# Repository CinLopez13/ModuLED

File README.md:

# ModuLED
Matriz led con doble función, Reloj Digital + Stacker Blocks

Es una Matriz de 18x7 que encontré en el LABI.

La idea es que tenga 2 funciones

Por un lado que sea un reloj digital para que quede en el LABI (a falta del reloj) 

Por otro lado quiero que tenga una función de "Game" para utilizar en los eventos del CDR (Como la feria del Libro o la Noche de los Museos). Este juego sería el stacker blocks

-> Dejo video de [Referencia](https://www.youtube.com/shorts/zlKPKK3Qink)

Para controlarlo decidí usar un modulo que controla matrices 8x8. Para cubrir todo el panel compré 3 modulos MAX7219 
Se va a programar con Arduino 

# Tareas 
- verificar que funcionan todos los Leds del panel 
- Soldar cables para conectar al modulo 
- Armar circuito con Arduino 
- Agregar mas Leds para hacer una matriz 24x7
- 

# Materiales
- Modulos MAX7219 x 3 
- Panel led del labi 
- Pines macho y hembra 
- Leds Rojo 3mm 
- Pistola de Silicona 

Objetivo: Una vez que funcione con Arduino la idea es programarlo con un ATMega del club (para esto hay que aprender a programar microcontroladores)

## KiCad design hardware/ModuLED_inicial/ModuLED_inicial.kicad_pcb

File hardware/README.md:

El modulo MAX7219 viene con un display 8x8 para usar. 
El objetivo es poder hacer esa matriz 8x8 (En realidad 8x7) pero con el panel que ya tenemos 

Se conectan al arduino VCC-GND-DIN-CS-CLK  Los pines donde esta DOUT son para conectar varios modulos 

Links de referencias para como utilizar el modulo MAX7219 

https://passionelectronique.fr/matrice-led-max7219-arduino/

https://www.pcbway.com/project/shareproject/LED_Dot_Matrix_MAX7219_1a67794a.html

https://www.14core.com/how-to-wire-8x8-matrix-led-with-max7219-on-arduino/

https://components101.com/displays/max7219-8x8-led-matrix-module

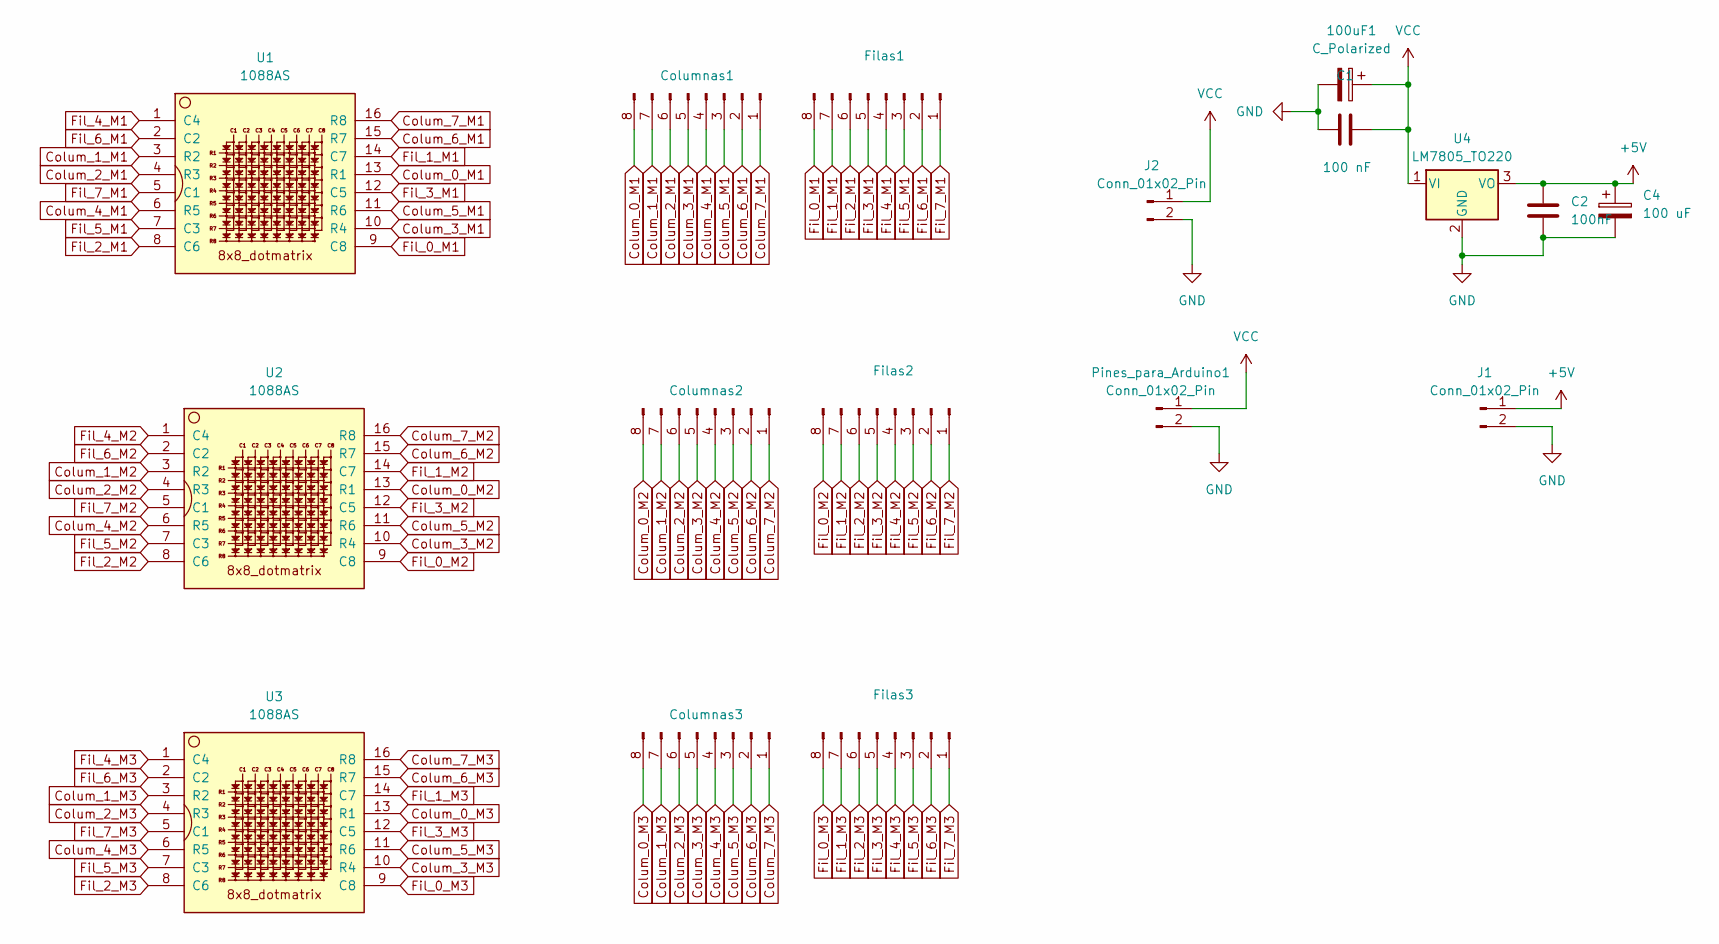
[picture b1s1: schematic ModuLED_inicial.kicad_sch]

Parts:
100uF1: C_Polarized; CP_Radial_D8.0mm_P2.50mm
C1: 100 nF; C_Disc_D3.4mm_W2.1mm_P2.50mm
C2: 100nF; C_Disc_D3.4mm_W2.1mm_P2.50mm
C4: 100 uF; CP_Radial_D8.0mm_P2.50mm
Columnas1, Columnas2, Columnas3: Conn_01x08_Pin; PinSocket_1x08_P2.54mm_Vertical
Filas1, Filas2, Filas3: Conn_01x08_Pin; PinSocket_1x08_P2.54mm_Vertical
J1: Conn_01x02_Pin; PinHeader_1x02_P2.54mm_Vertical
J2: Conn_01x02_Pin; Molex_KK-396_A-41791-0002_1x02_P3.96mm_Vertical
Pines_para_Arduino1: Conn_01x02_Pin; PinHeader_1x02_P2.54mm_Vertical
U1, U2, U3: 1088AS; LED_1088_Pin_Header
U4: LM7805_TO220; TO-220-3_Vertical

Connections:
+5V: C2.1, C4.1, J1.1, U4.3 (VO)
Colum_0_M1: Columnas1.8, U1.13 (R1)
Colum_0_M2: Columnas2.8, U2.13 (R1)
Colum_0_M3: Columnas3.8, U3.13 (R1)
Colum_1_M1: Columnas1.7, U1.3 (R2)
Colum_1_M2: Columnas2.7, U2.3 (R2)
Colum_1_M3: Columnas3.7, U3.3 (R2)
Colum_2_M1: Columnas1.6, U1.4 (R3)
Colum_2_M2: Columnas2.6, U2.4 (R3)
Colum_2_M3: Columnas3.6, U3.4 (R3)
Colum_3_M1: Columnas1.5, U1.10 (R4)
Colum_3_M2: Columnas2.5, U2.10 (R4)
Colum_3_M3: Columnas3.5, U3.10 (R4)
Colum_4_M1: Columnas1.4, U1.6 (R5)
Colum_4_M2: Columnas2.4, U2.6 (R5)
Colum_4_M3: Columnas3.4, U3.6 (R5)
Colum_5_M1: Columnas1.3, U1.11 (R6)
Colum_5_M2: Columnas2.3, U2.11 (R6)
Colum_5_M3: Columnas3.3, U3.11 (R6)
Colum_6_M1: Columnas1.2, U1.15 (R7)
Colum_6_M2: Columnas2.2, U2.15 (R7)
Colum_6_M3: Columnas3.2, U3.15 (R7)
Colum_7_M1: Columnas1.1, U1.16 (R8)
Colum_7_M2: Columnas2.1, U2.16 (R8)
Colum_7_M3: Columnas3.1, U3.16 (R8)
Fil_0_M1: Filas1.8, U1.9 (C8)
Fil_0_M2: Filas2.8, U2.9 (C8)
Fil_0_M3: Filas3.8, U3.9 (C8)
Fil_1_M1: Filas1.7, U1.14 (C7)
Fil_1_M2: Filas2.7, U2.14 (C7)
Fil_1_M3: Filas3.7, U3.14 (C7)
Fil_2_M1: Filas1.6, U1.8 (C6)
Fil_2_M2: Filas2.6, U2.8 (C6)
Fil_2_M3: Filas3.6, U3.8 (C6)
Fil_3_M1: Filas1.5, U1.12 (C5)
Fil_3_M2: Filas2.5, U2.12 (C5)
Fil_3_M3: Filas3.5, U3.12 (C5)
Fil_4_M1: Filas1.4, U1.1 (C4)
Fil_4_M2: Filas2.4, U2.1 (C4)
Fil_4_M3: Filas3.4, U3.1 (C4)
Fil_5_M1: Filas1.3, U1.7 (C3)
Fil_5_M2: Filas2.3, U2.7 (C3)
Fil_5_M3: Filas3.3, U3.7 (C3)
Fil_6_M1: Filas1.2, U1.2 (C2)
Fil_6_M2: Filas2.2, U2.2 (C2)
Fil_6_M3: Filas3.2, U3.2 (C2)
Fil_7_M1: Filas1.1, U1.5 (C1)
Fil_7_M2: Filas2.1, U2.5 (C1)
Fil_7_M3: Filas3.1, U3.5 (C1)
GND: 100uF1.2, C1.1, C2.2, C4.2, J1.2, J2.2, Pines_para_Arduino1.2, U4.2 (GND)
VCC: 100uF1.1, C1.2, J2.1, Pines_para_Arduino1.1, U4.1 (VI)

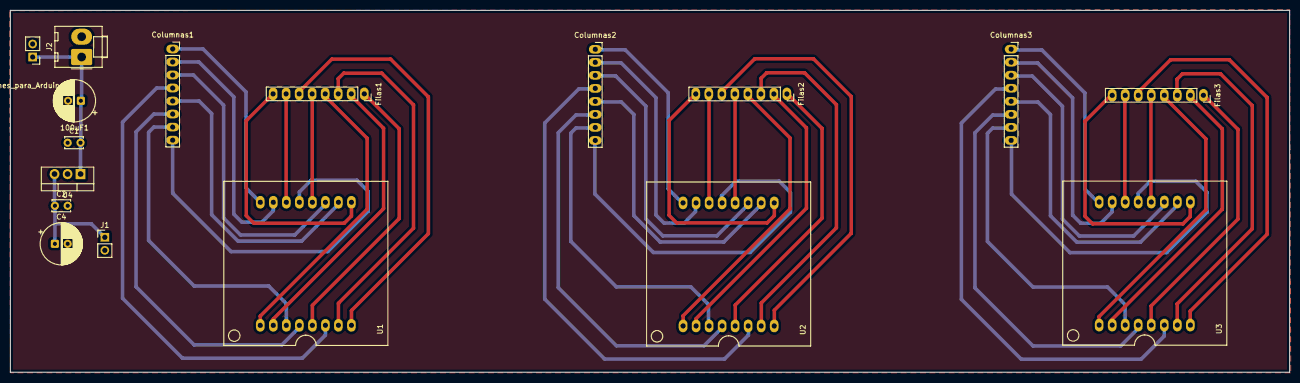
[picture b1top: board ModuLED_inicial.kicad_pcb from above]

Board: 2 copper layers, 249.5 x 70.6 mm, 17 parts (0 on the bottom side), 51 nets.

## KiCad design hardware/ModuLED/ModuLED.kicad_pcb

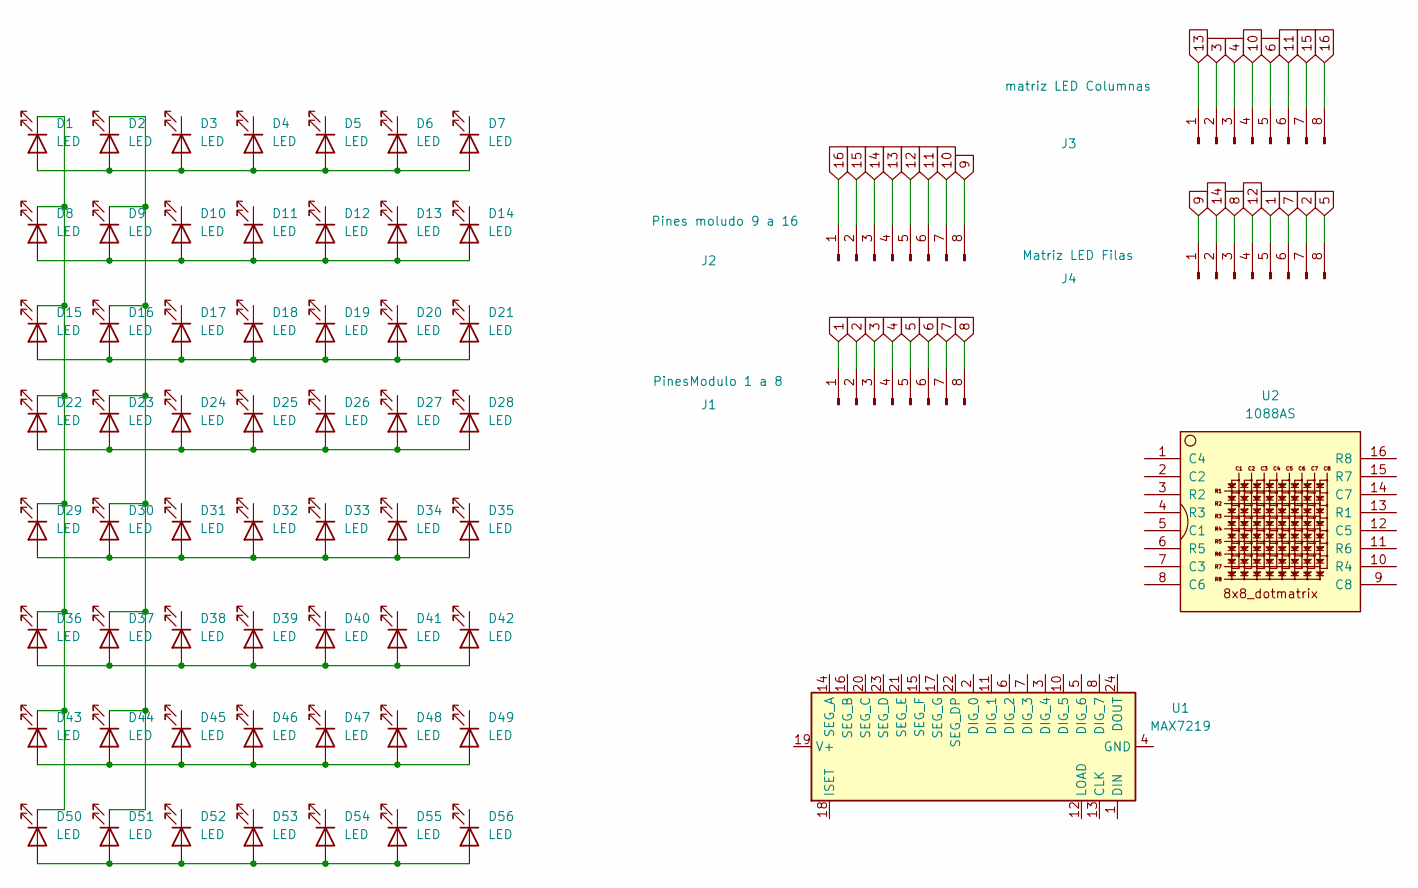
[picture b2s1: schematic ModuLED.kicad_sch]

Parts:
D1, D2, D3, D4, D5, D6, D7, D8, D9, D10, D11, D12, D13, D14, D15, D16, D17, D18, D19, D20, D21, D22, D23, D24, D25, D26, D27, D28, D29, D30, D31, D32, D33, D34, D35, D36, D37, D38, D39, D40, D41, D42, D43, D44, D45, D46, D47, D48, D49, D50, D51, D52, D53, D54, D55, D56: LED; LED_D3.0mm_Clear
J1: PinesModulo 1 a 8; Hirose_DF13-08P-1.25DSA_1x08_P1.25mm_Vertical
J2: Pines moludo 9 a 16; Hirose_DF13-08P-1.25DSA_1x08_P1.25mm_Vertical
J3: matriz LED Columnas; Hirose_DF13-08P-1.25DSA_1x08_P1.25mm_Vertical
J4: Matriz LED Filas; Hirose_DF13-08P-1.25DSA_1x08_P1.25mm_Vertical
U1: MAX7219; DIP-24_W7.62mm
U2: 1088AS; LED_1088_Pin_Header

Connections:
1: J1.1, J4.5
2: J1.2, J4.7
3: J1.3, J3.2
4: J1.4, J3.3
5: J1.5, J4.8
6: J1.6, J3.5
7: J1.7, J4.6
8: J1.8, J4.3
9: J2.8, J4.1
10: J2.7, J3.4
11: J2.6, J3.6
12: J2.5, J4.4
13: J2.4, J3.1
14: J2.3, J4.2
15: J2.2, J3.7
16: J2.1, J3.8
unnamed: D1.2 (A), D2.2 (A), D3.2 (A), D4.2 (A), D5.2 (A), D6.2 (A), D7.2 (A)
unnamed: D1.1 (K), D8.1 (K), D15.1 (K), D22.1 (K), D29.1 (K), D36.1 (K), D43.1 (K), D50.1 (K)
unnamed: D8.2 (A), D9.2 (A), D10.2 (A), D11.2 (A), D12.2 (A), D13.2 (A), D14.2 (A)
unnamed: D15.2 (A), D16.2 (A), D17.2 (A), D18.2 (A), D19.2 (A), D20.2 (A), D21.2 (A)
unnamed: D2.1 (K), D9.1 (K), D16.1 (K), D23.1 (K), D30.1 (K), D37.1 (K), D44.1 (K), D51.1 (K)
unnamed: D22.2 (A), D23.2 (A), D24.2 (A), D25.2 (A), D26.2 (A), D27.2 (A), D28.2 (A)
unnamed: D29.2 (A), D30.2 (A), D31.2 (A), D32.2 (A), D33.2 (A), D34.2 (A), D35.2 (A)
unnamed: D36.2 (A), D37.2 (A), D38.2 (A), D39.2 (A), D40.2 (A), D41.2 (A), D42.2 (A)
unnamed: D43.2 (A), D44.2 (A), D45.2 (A), D46.2 (A), D47.2 (A), D48.2 (A), D49.2 (A)
unnamed: D50.2 (A), D51.2 (A), D52.2 (A), D53.2 (A), D54.2 (A), D55.2 (A), D56.2 (A)
unnamed: U1.4 (GND), U1.9 (GND)

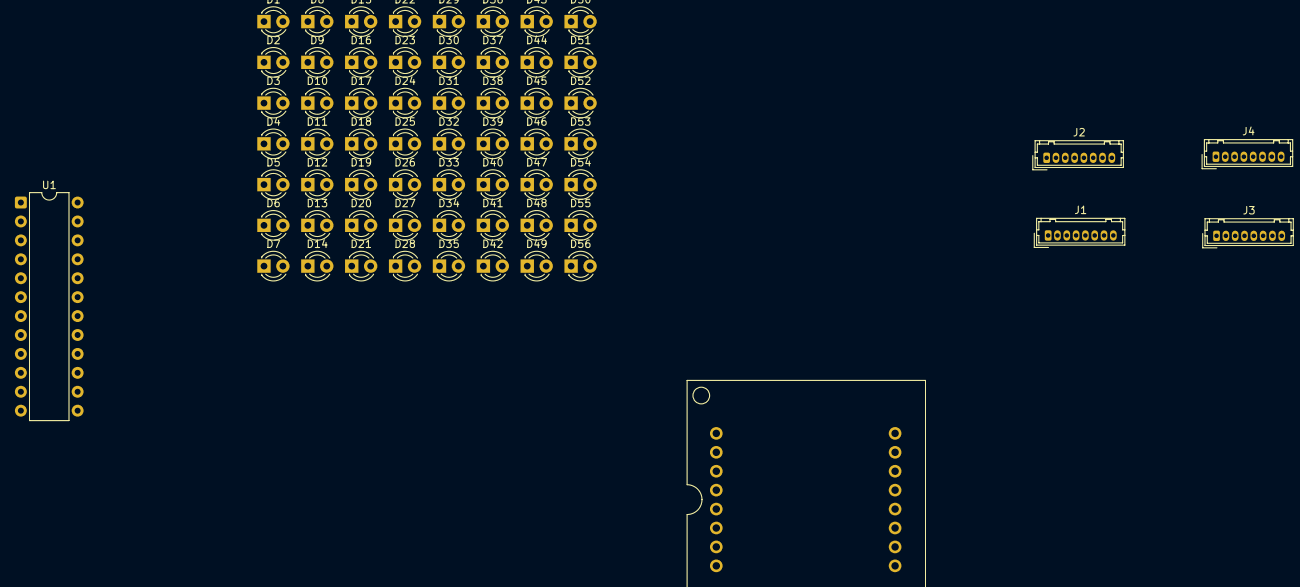
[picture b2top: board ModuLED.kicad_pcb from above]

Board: 2 copper layers, 62 parts (0 on the bottom side), 27 nets.

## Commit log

2025-09-25 Carpeta de fotos
2025-09-26 Agrego Carpetas
2025-09-26 Esquemático
2025-09-26 Modulo y Display
2025-09-26 kicad
2025-09-26 imagen
2025-09-26 fotos
2025-09-26 pines arduino
2025-09-27 codigos
2025-10-08 agrego diario con ideas a implementar
2025-10-12 Diseño
    Se sumo el esquemático y huella del display 1088 y arme un nuevo proyecto en kiCAD para ver como conectar los pines en la primera version de la placa
2025-11-03 Primera Placa
    Diseño de la primera placa para esta matriz, hecha para que tenga alimentación por batería con un regulador y los pines para sacar loscables que conecten a las entradas y salidas de los modulos. Desp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
